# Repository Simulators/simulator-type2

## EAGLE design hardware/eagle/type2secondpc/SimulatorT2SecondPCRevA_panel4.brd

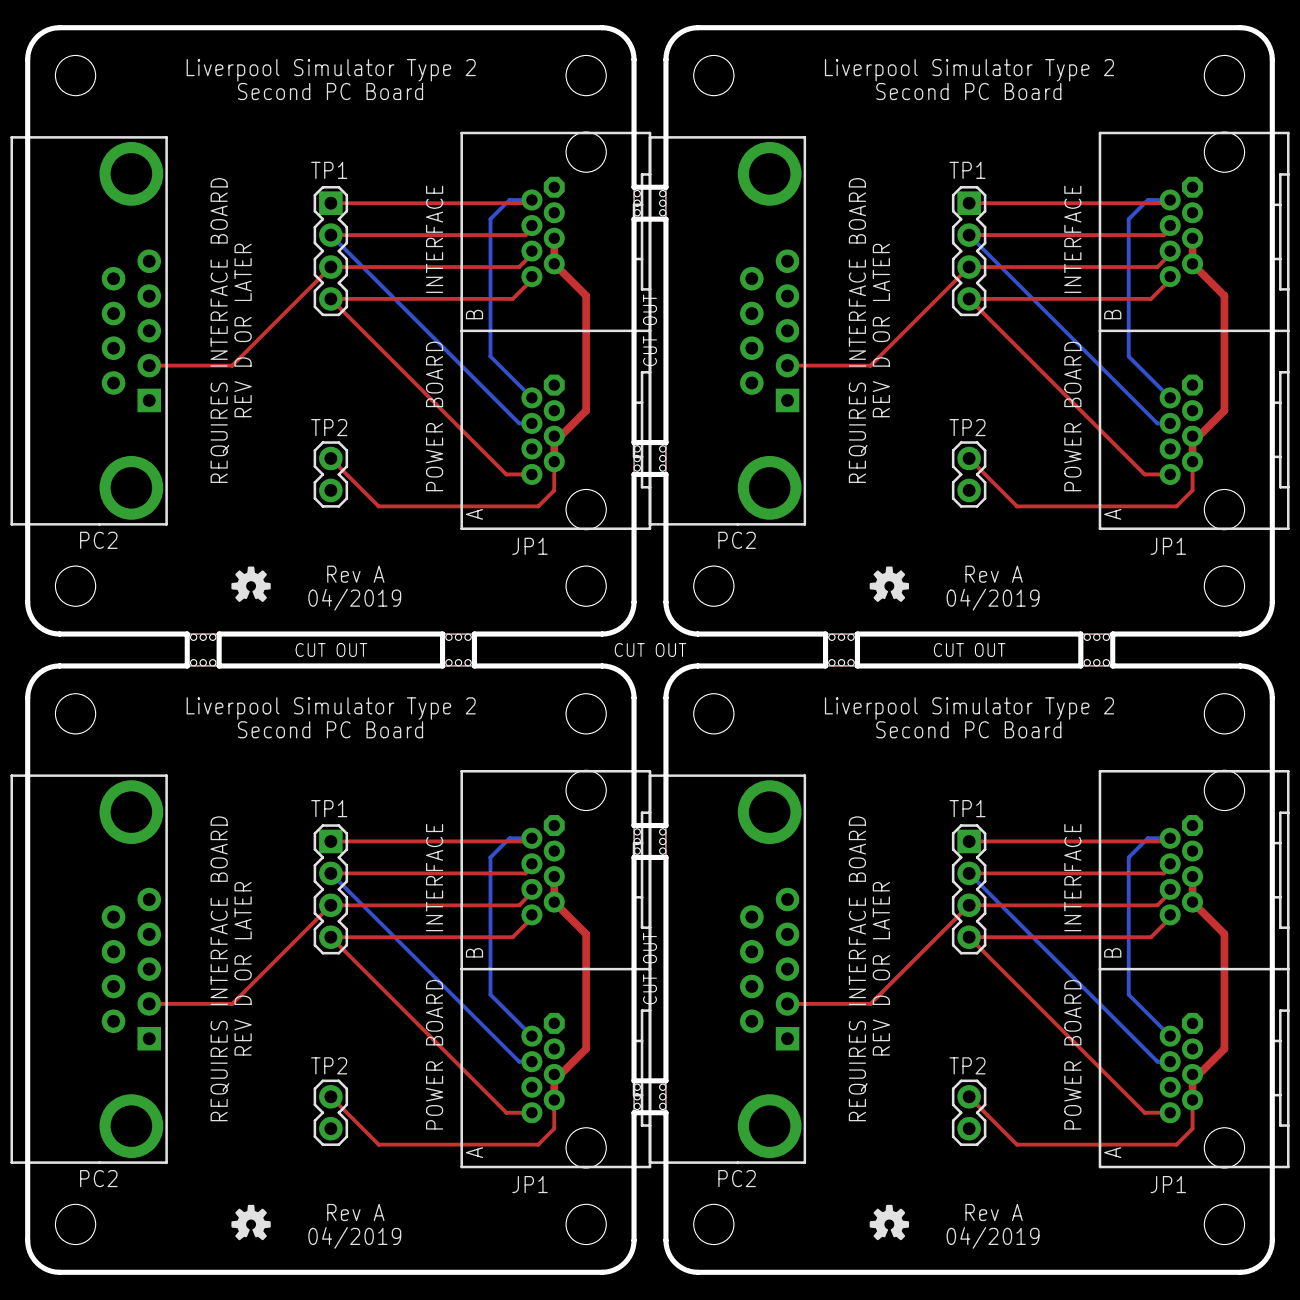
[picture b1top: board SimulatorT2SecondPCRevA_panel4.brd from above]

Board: 2 copper layers, 99.1 x 99.1 mm, 28 parts (0 on the bottom side), 24 nets.

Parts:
E$1, E$2, E$3, E$4, E$5, E$6, E$7, E$8: STAMP_HOLES
JP1, JP1_1, JP1_2, JP1_3: RJ45-RJHSE-5080-022HOLE; RJ45-RJHSE-5080-02
LOGO1, LOGO1_1, LOGO1_2, LOGO1_3: OSHW-LOGOS; OSHW-LOGO-S
PC2, PC2_1, PC2_2, PC2_3: MULTICOMP-DB9-FEMALE-PCB-90DEG
TP1, TP1_1, TP1_2, TP1_3: 1X04
TP2, TP2_1, TP2_2, TP2_3: 1X02

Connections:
GND: JP1.A1, JP1.A3, JP1.B1, JP1.B3, PC2.5, TP2.2
GND1: JP1_1.A1, JP1_1.A3, JP1_1.B1, JP1_1.B3, PC2_1.5, TP2_1.2
GND2: JP1_2.A1, JP1_2.A3, JP1_2.B1, JP1_2.B3, PC2_2.5, TP2_2.2
GND3: JP1_3.A1, JP1_3.A3, JP1_3.B1, JP1_3.B3, PC2_3.5, TP2_3.2
P8: JP1.A8, JP1.B8, TP1.4
P81: JP1_1.A8, JP1_1.B8, TP1_1.4
P82: JP1_2.A8, JP1_2.B8, TP1_2.4
P83: JP1_3.A8, JP1_3.B8, TP1_3.4
RXD: JP1.A4, JP1.B4, TP1.2
RXD1: JP1_1.A4, JP1_1.B4, TP1_1.2
RXD2: JP1_2.A4, JP1_2.B4, TP1_2.2
RXD3: JP1_3.A4, JP1_3.B4, TP1_3.2
TX2: JP1.B6, PC2.2, TP1.3
TX21: JP1_1.B6, PC2_1.2, TP1_1.3
TX22: JP1_2.B6, PC2_2.2, TP1_2.3
TX23: JP1_3.B6, PC2_3.2, TP1_3.3
TXD: JP1.A2, JP1.B2, TP1.1
TXD1: JP1_1.A2, JP1_1.B2, TP1_1.1
TXD2: JP1_2.A2, JP1_2.B2, TP1_2.1
TXD3: JP1_3.A2, JP1_3.B2, TP1_3.1
VIN2: JP1.A5, JP1.A7, JP1.B5, JP1.B7, TP2.1
VIN21: JP1_1.A5, JP1_1.A7, JP1_1.B5, JP1_1.B7, TP2_1.1
VIN22: JP1_2.A5, JP1_2.A7, JP1_2.B5, JP1_2.B7, TP2_2.1
VIN23: JP1_3.A5, JP1_3.A7, JP1_3.B5, JP1_3.B7, TP2_3.1

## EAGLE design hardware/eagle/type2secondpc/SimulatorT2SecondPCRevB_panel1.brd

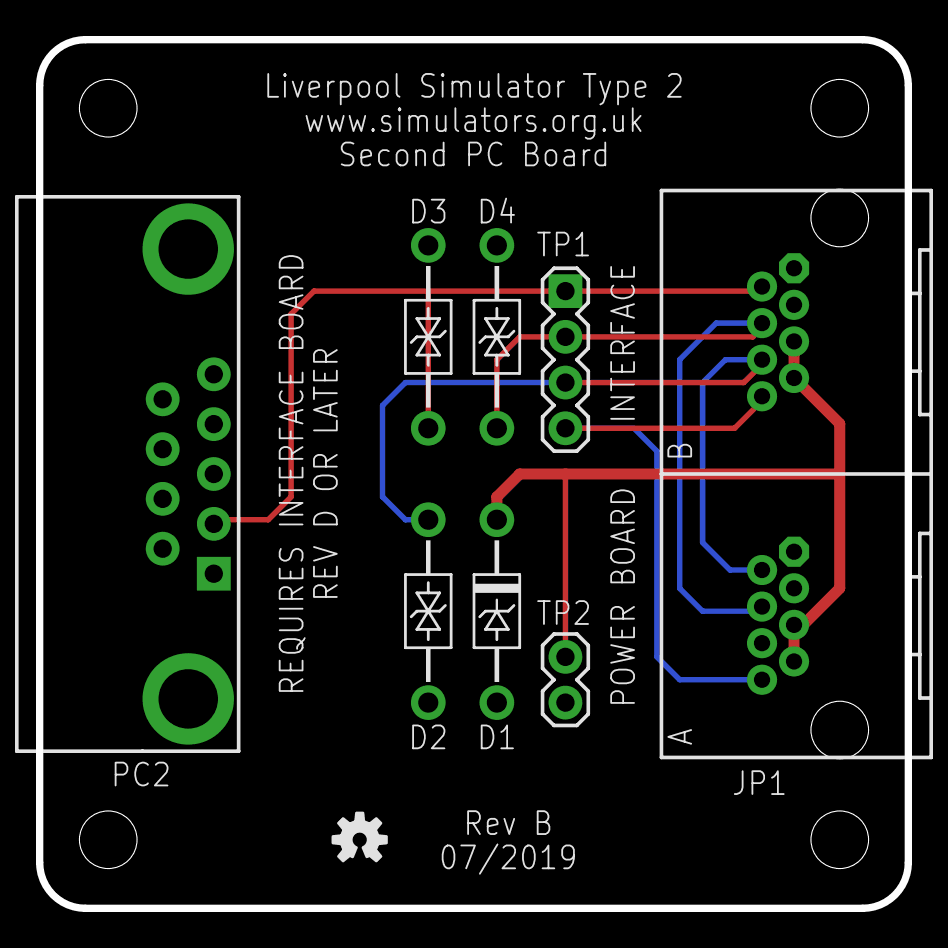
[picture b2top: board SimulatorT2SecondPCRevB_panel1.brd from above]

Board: 2 copper layers, 48.3 x 48.3 mm, 10 parts (1 on the bottom side), 6 nets.

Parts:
D1: SA12A; DO41_TVS_UNI
D2, D3, D4: SA15CA; DO41_TVS_BI
E$1: WARNING_TRIANGLE_TPLACE
JP1: RJ45-RJHSE-5080-022HOLE; RJ45-RJHSE-5080-02
LOGO1: OSHW-LOGOS; OSHW-LOGO-S
PC2: MULTICOMP-DB9-FEMALE-PCB-90DEG
TP1: 1X04
TP2: 1X02

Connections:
GND: D1.ANODE, D2.A, D3.A, D4.A, JP1.A1, JP1.A3, JP1.B1, JP1.B3, PC2.5, TP2.2
P8: JP1.A8, JP1.B8, TP1.4
RXD: D4.C, JP1.A4, JP1.B4, TP1.2
TX2: D2.C, JP1.A2, JP1.B6, TP1.3
TXD: D3.C, JP1.B2, PC2.2, TP1.1
VIN2: D1.CATHODE, JP1.A5, JP1.A7, JP1.B5, JP1.B7, TP2.1

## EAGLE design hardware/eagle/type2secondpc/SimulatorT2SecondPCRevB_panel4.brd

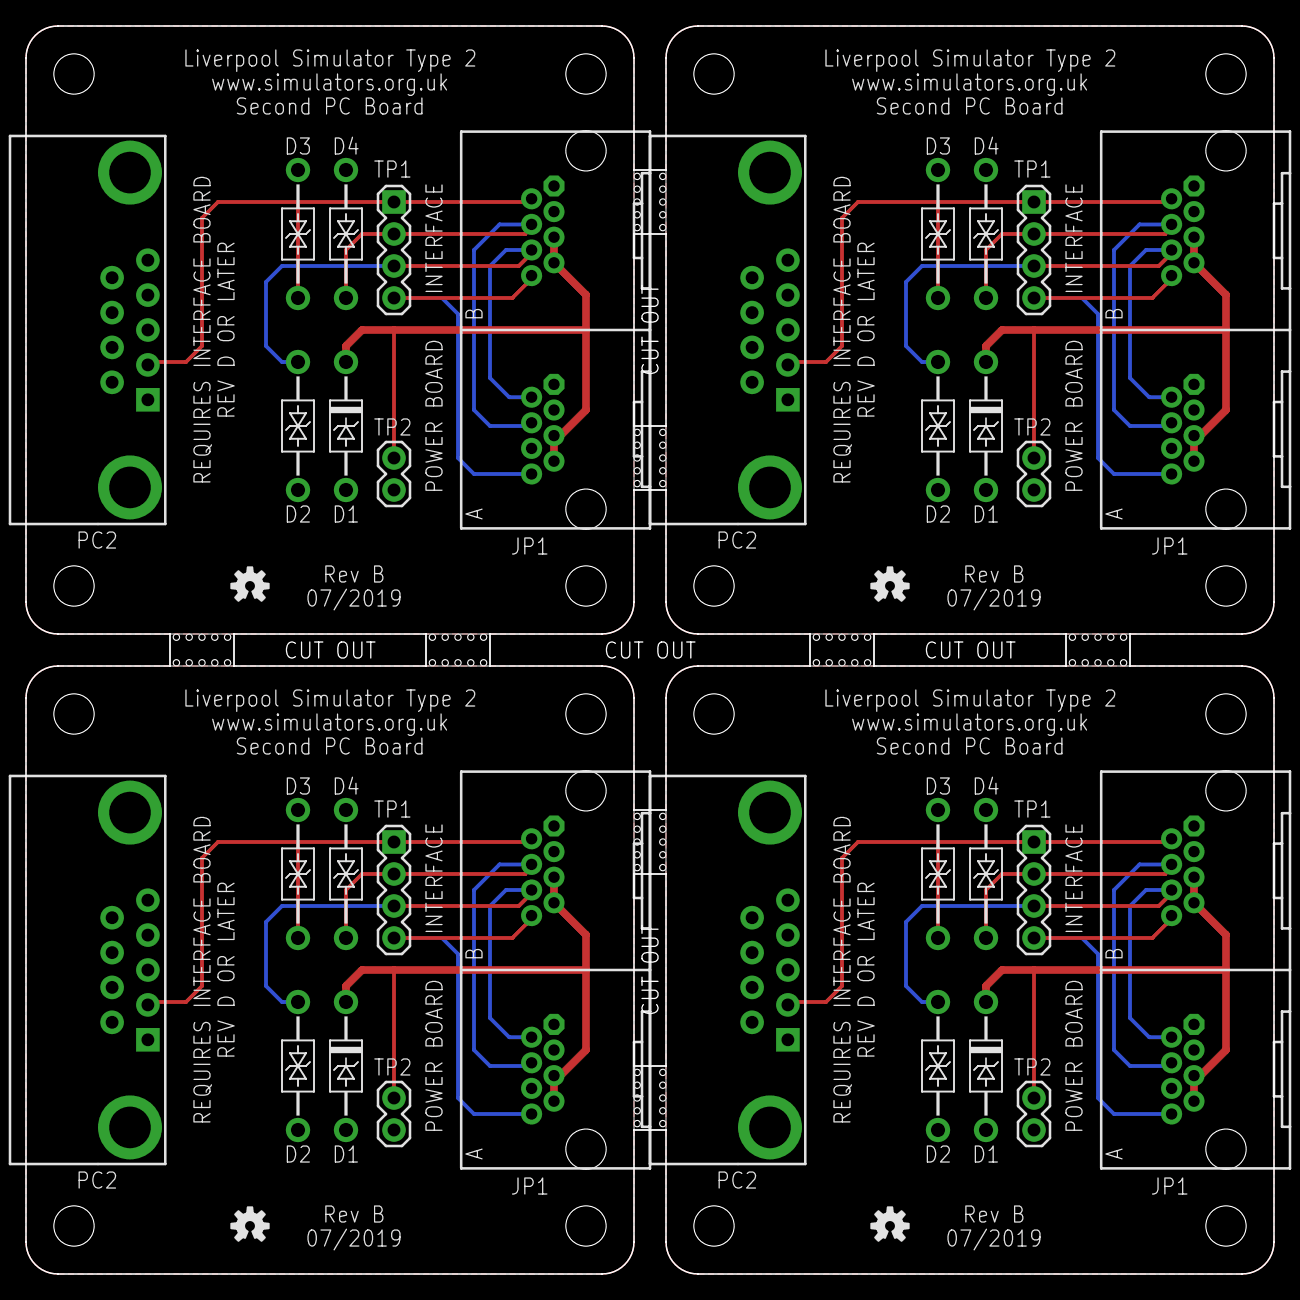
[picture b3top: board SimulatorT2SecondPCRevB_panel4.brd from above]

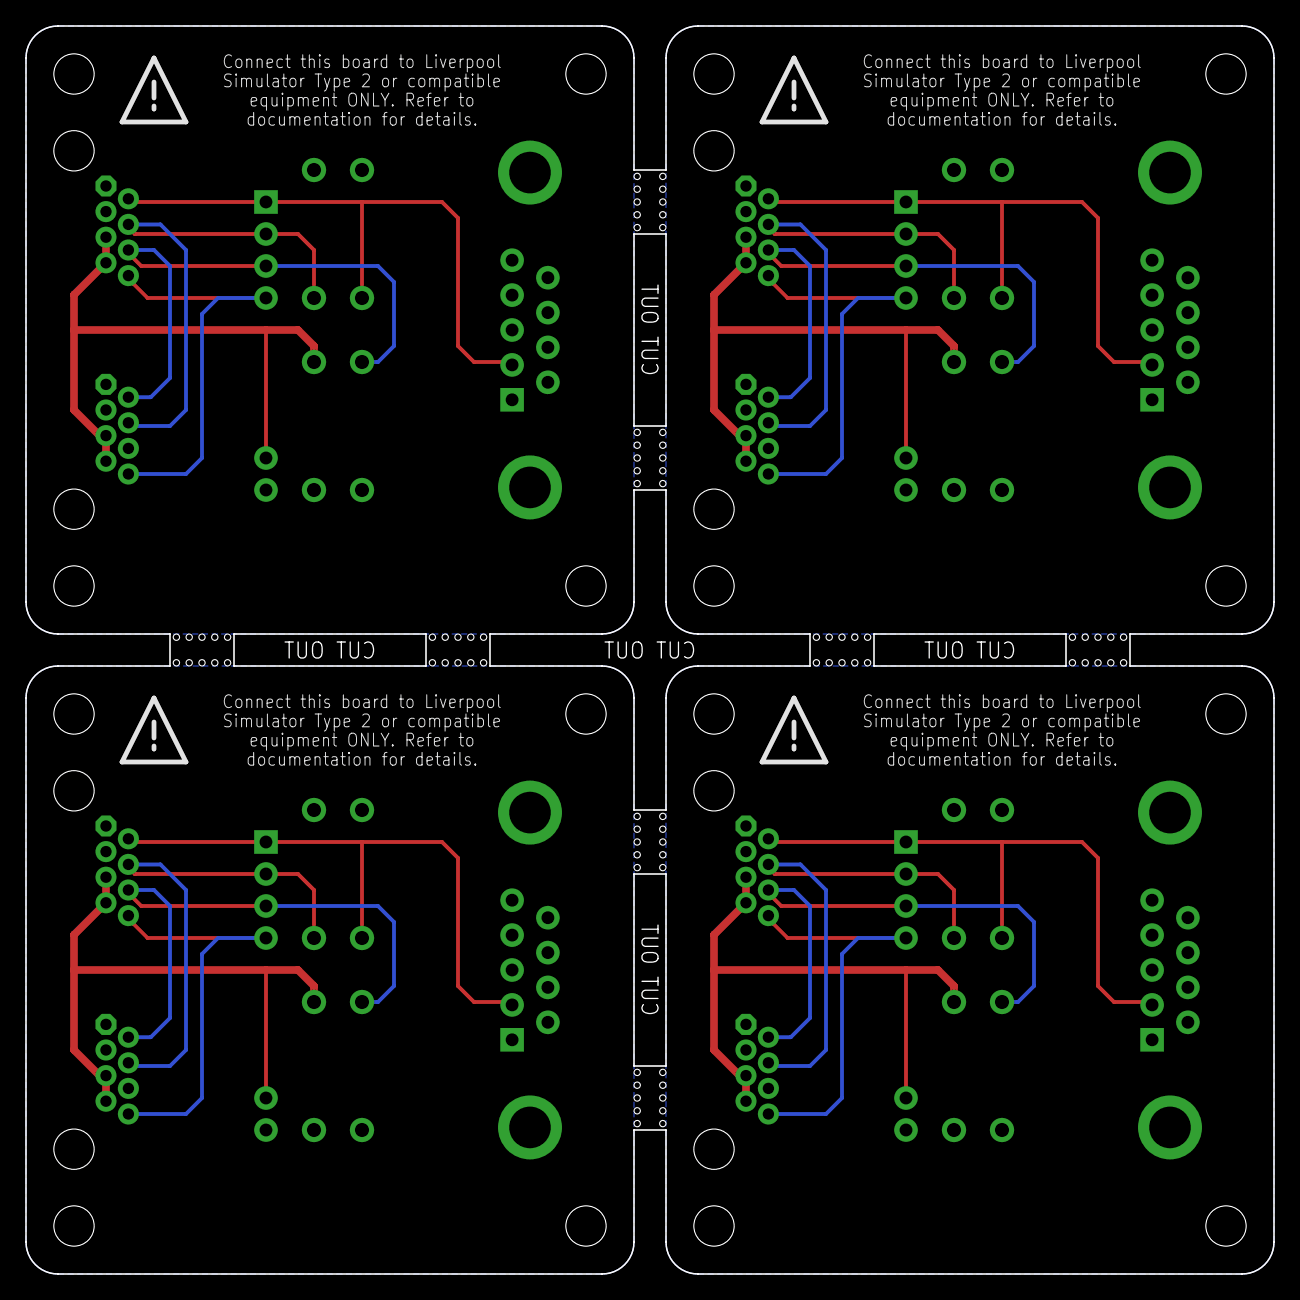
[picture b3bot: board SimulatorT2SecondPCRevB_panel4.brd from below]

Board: 2 copper layers, 99.1 x 99.1 mm, 41 parts (4 on the bottom side), 24 nets.

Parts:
D1, D1_1, D1_2, D1_3: SA12A; DO41_TVS_UNI
D2, D2_1, D2_2, D2_3, D3, D3_1, D3_2, D3_3, D4, D4_1, D4_2, D4_3: SA15CA; DO41_TVS_BI
E$1: OUTLINE_PANEL_4_5MM
E$2, E$3, E$4, E$5: WARNING_TRIANGLE_TPLACE
JP1, JP1_1, JP1_2, JP1_3: RJ45-RJHSE-5080-022HOLE; RJ45-RJHSE-5080-02
LOGO1, LOGO1_1, LOGO1_2, LOGO1_3: OSHW-LOGOS; OSHW-LOGO-S
PC2, PC2_1, PC2_2, PC2_3: MULTICOMP-DB9-FEMALE-PCB-90DEG
TP1, TP1_1, TP1_2, TP1_3: 1X04
TP2, TP2_1, TP2_2, TP2_3: 1X02

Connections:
GND: D1.ANODE, D2.A, D3.A, D4.A, JP1.A1, JP1.A3, JP1.B1, JP1.B3, PC2.5, TP2.2
GND1: D1_1.ANODE, D2_1.A, D3_1.A, D4_1.A, JP1_1.A1, JP1_1.A3, JP1_1.B1, JP1_1.B3, PC2_1.5, TP2_1.2
GND2: D1_2.ANODE, D2_2.A, D3_2.A, D4_2.A, JP1_2.A1, JP1_2.A3, JP1_2.B1, JP1_2.B3, PC2_2.5, TP2_2.2
GND3: D1_3.ANODE, D2_3.A, D3_3.A, D4_3.A, JP1_3.A1, JP1_3.A3, JP1_3.B1, JP1_3.B3, PC2_3.5, TP2_3.2
P8: JP1.A8, JP1.B8, TP1.4
P81: JP1_1.A8, JP1_1.B8, TP1_1.4
P82: JP1_2.A8, JP1_2.B8, TP1_2.4
P83: JP1_3.A8, JP1_3.B8, TP1_3.4
RXD: D4.C, JP1.A4, JP1.B4, TP1.2
RXD1: D4_1.C, JP1_1.A4, JP1_1.B4, TP1_1.2
RXD2: D4_2.C, JP1_2.A4, JP1_2.B4, TP1_2.2
RXD3: D4_3.C, JP1_3.A4, JP1_3.B4, TP1_3.2
TX2: D2.C, JP1.A2, JP1.B6, TP1.3
TX21: D2_1.C, JP1_1.A2, JP1_1.B6, TP1_1.3
TX22: D2_2.C, JP1_2.A2, JP1_2.B6, TP1_2.3
TX23: D2_3.C, JP1_3.A2, JP1_3.B6, TP1_3.3
TXD: D3.C, JP1.B2, PC2.2, TP1.1
TXD1: D3_1.C, JP1_1.B2, PC2_1.2, TP1_1.1
TXD2: D3_2.C, JP1_2.B2, PC2_2.2, TP1_2.1
TXD3: D3_3.C, JP1_3.B2, PC2_3.2, TP1_3.1
VIN2: D1.CATHODE, JP1.A5, JP1.A7, JP1.B5, JP1.B7, TP2.1
VIN21: D1_1.CATHODE, JP1_1.A5, JP1_1.A7, JP1_1.B5, JP1_1.B7, TP2_1.1
VIN22: D1_2.CATHODE, JP1_2.A5, JP1_2.A7, JP1_2.B5, JP1_2.B7, TP2_2.1
VIN23: D1_3.CATHODE, JP1_3.A5, JP1_3.A7, JP1_3.B5, JP1_3.B7, TP2_3.1

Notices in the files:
parts and their libraries:
SparkFun-Aesthetics: Licensing: Creative Commons ShareAlike 4.0 International - https://creativecommons.org/licenses/by-sa/4.0
